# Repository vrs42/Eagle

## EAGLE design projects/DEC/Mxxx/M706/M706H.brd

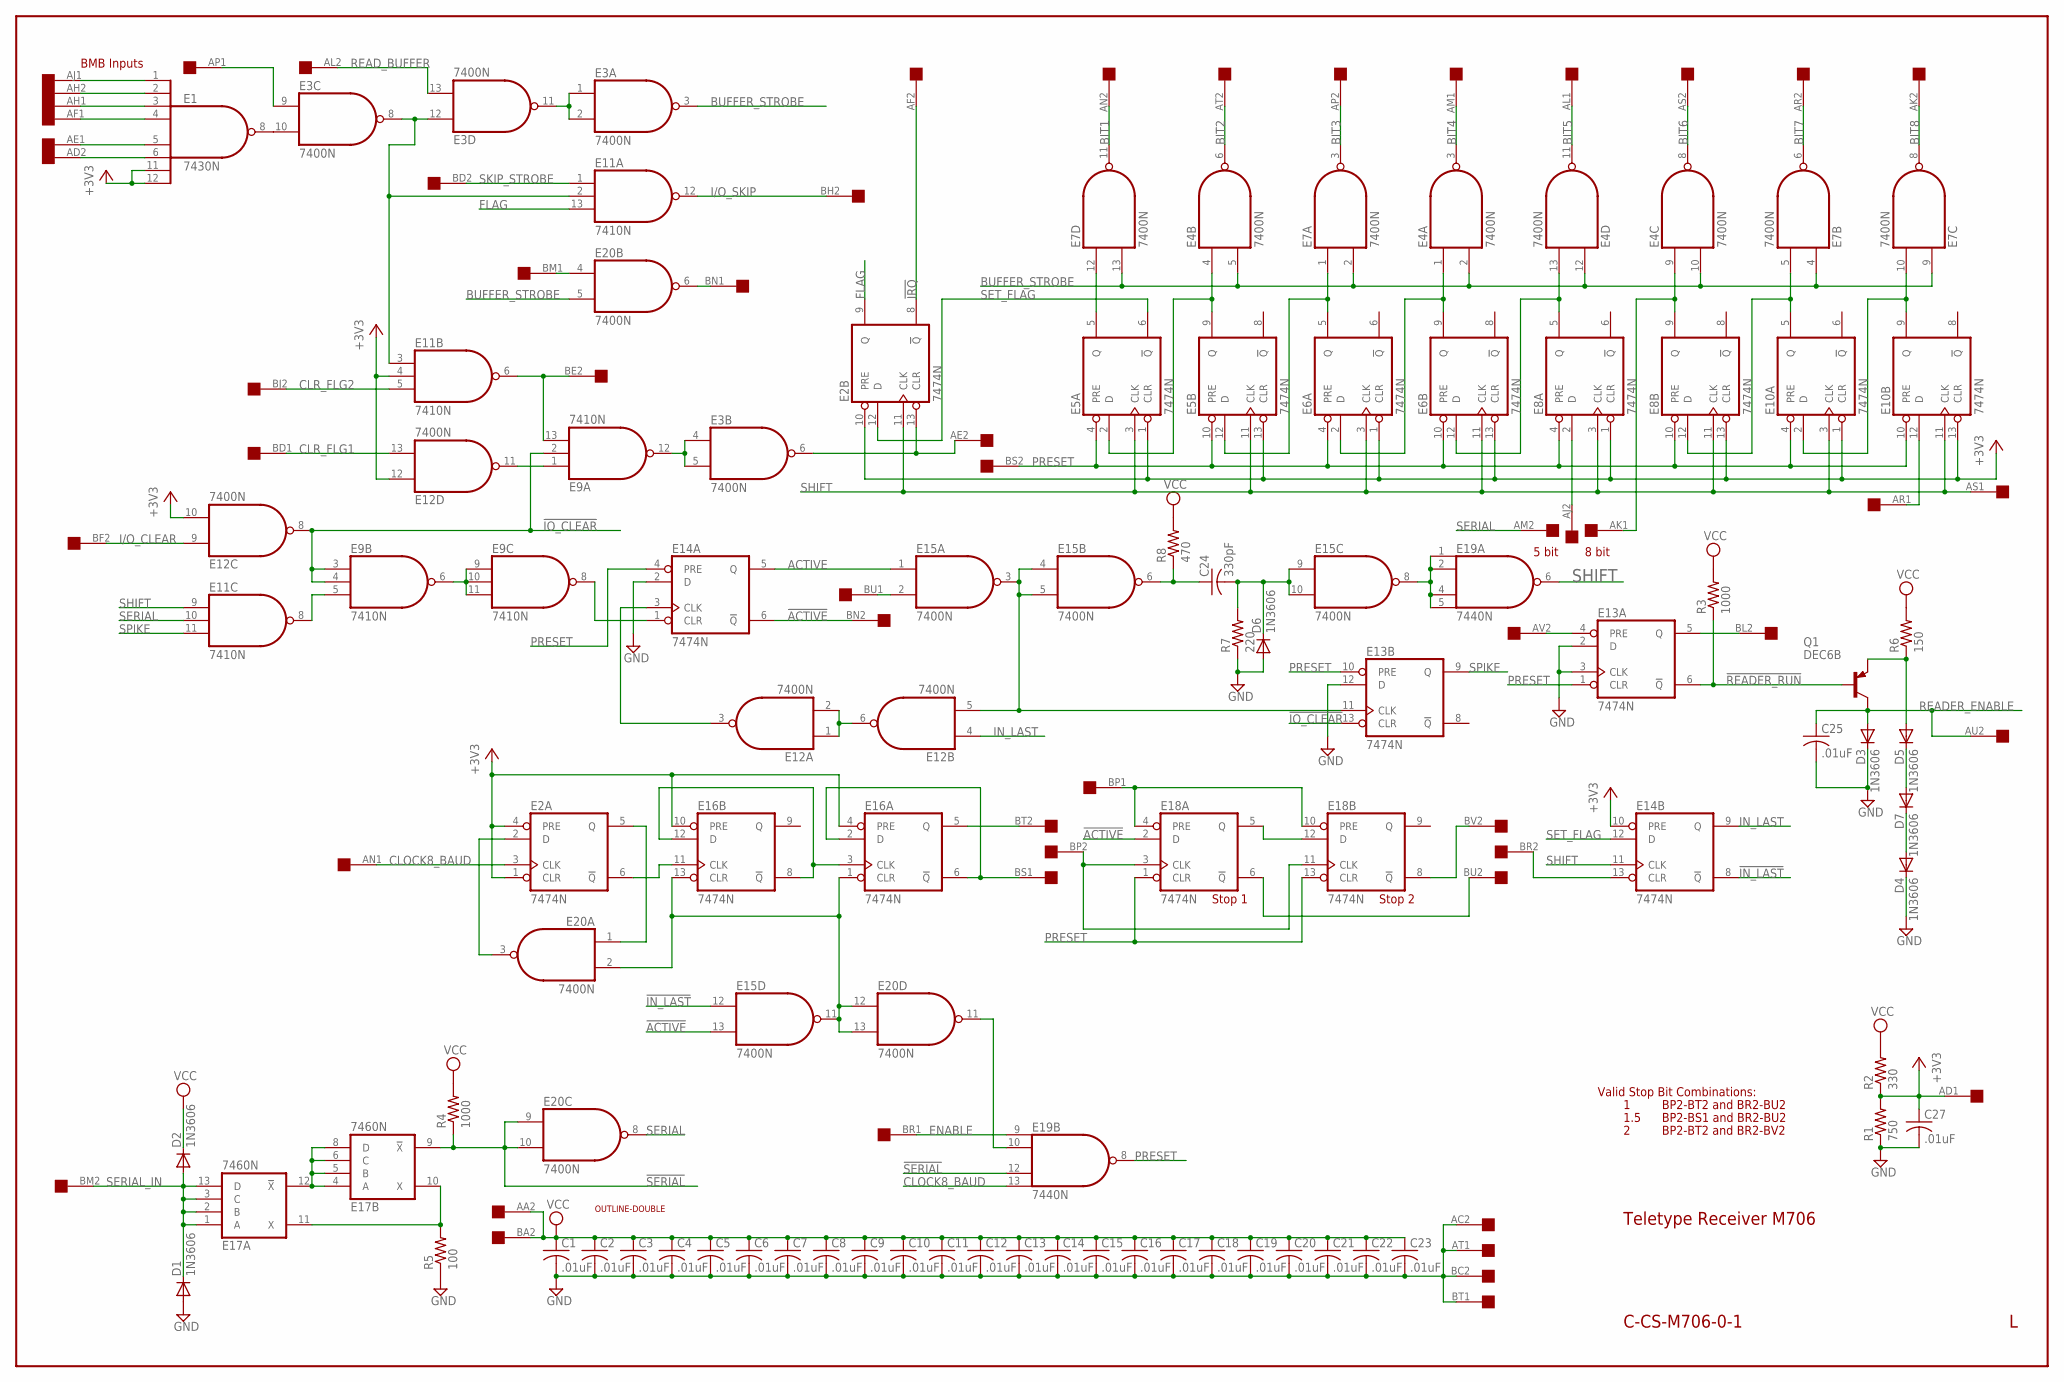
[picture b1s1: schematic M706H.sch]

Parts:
C1, C2, C3, C4, C5, C6, C7, C8, C9, C10, C11, C12, C13, C14, C15, C16, C17, C18, C19, C20, C21, C22, C23, C25, C27: .01uF; C050-025X075
C24: 330pF; C050-025X075
D1, D2, D3, D4, D5, D6, D7: 1N3606; DO35-10
E1: 7430N; DIL14
E2, E5, E6, E8, E10, E13, E14, E16, E18: 7474N; DIL14
E3, E4, E7, E12, E15, E20: 7400N; DIL14
E9, E11: 7410N; DIL14
E17: 7460N; DIL14
E19: 7440N; DIL14
Q1: DEC6B; TO39
R1: 750; 0207/10
R2: 330; 0207/10
R3, R4: 1000; 0207/10
R5: 100; 0207/10
R6: 150; 0207/10
R7: 220; 0207/10
R8: 470; 0207/10
U$1: OUTLINE-DOUBLE; DOUBLE
U$2: DOUBLE; EDGE-CON4

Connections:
2^0: E2.5 (Q), E20.1 (I0)
!ACTIVE: E14.6 (!Q), E15.13 (I1), E18.2 (D), U$2.BN2
!IN_LAST: E14.8 (!Q), E15.12 (I0)
!IO_CLEAR: E9.2 (I1), E9.3 (I0), E9.4 (I1), E12.8 (O), E13.13 (CLR)
!IRQ: E2.8 (!Q), U$2.AF2
!READER_RUN: E13.6 (!Q), Q1.2 (B), R3.1
!SERIAL: E17.9 (!X), E19.12 (I2), E20.9 (I0), E20.10 (I1), R4.1
+3V3: C27.1, E1.11 (I6), E1.12 (I7), E2.1 (CLR), E2.4 (PRE), E2.10 (PRE), E5.1 (CLR), E5.13 (CLR), E6.1 (CLR), E6.13 (CLR), E8.1 (CLR), E8.13 (CLR), E10.1 (CLR), E10.13 (CLR), E11.4 (I1), E12.10 (I1), E12.12 (I0), E14.10 (PRE), E16.4 (PRE), E16.10 (PRE), R1.2, R2.1, U$2.AD1
ACTIVE: E14.5 (Q), E15.1 (I0)
BIT1: E7.11 (O), U$2.AN2
BIT2: E4.6 (O), U$2.AT2
BIT3: E7.3 (O), U$2.AP2
BIT4: E4.3 (O), U$2.AM1
BIT5: E4.11 (O), U$2.AL1
BIT6: E4.8 (O), U$2.AS2
BIT7: E7.6 (O), U$2.AR2
BIT8: E7.8 (O), U$2.AK2
BUFFER_STROBE: E3.3 (O), E4.2 (I1), E4.5 (I1), E4.10 (I1), E4.12 (I0), E7.2 (I1), E7.4 (I0), E7.9 (I0), E7.13 (I1), E20.5 (I1)
CLOCK8_BAUD: E2.3 (CLK), E19.13 (I3), U$2.AN1
CLR_FLG1: E12.13 (I1), U$2.BD1
CLR_FLG2: E11.5 (I2), U$2.BJ2
ENABLE: E19.9 (I0), U$2.BR1
FLAG: E2.9 (Q), E11.13 (I2)
GND: C1.2, C2.2, C3.2, C4.2, C5.2, C6.2, C7.2, C8.2, C9.2, C10.2, C11.2, C12.2, C13.2, C14.2, C15.2, C16.2, C17.2, C18.2, C19.2, C20.2, C21.2, C22.2, C23.2, C25.2, C27.2, D1.A, D3.C, D4.C, D6.A, E1.7 (GND), E2.7 (GND), E3.7 (GND), E4.7 (GND), E5.7 (GND), E6.7 (GND), E7.7 (GND), E8.7 (GND), E9.7 (GND), E10.7 (GND), E11.7 (GND), E12.7 (GND), E13.2 (D), E13.3 (CLK), E13.7 (GND), E13.12 (D), E14.2 (D), E14.7 (GND), E15.7 (GND), E16.7 (GND), E17.7 (GND), E18.7 (GND), E19.7 (GND), E20.7 (GND), R1.1, R5.1, R7.1, U$2.AC2, U$2.AT1, U$2.BC2, U$2.BT1
I/O_CLEAR: E12.9 (I0), U$2.BF2
I/O_SKIP: E11.12 (O), U$2.BH2
IN_LAST: E12.4 (I0), E14.9 (Q)
unnamed: E19.10 (I1), E20.11 (O)
unnamed: E7.5 (I1), E8.12 (D), E10.5 (Q)
unnamed: E7.10 (I1), E10.2 (D), E10.9 (Q)
unnamed: E4.9 (I0), E8.9 (Q), U$2.AK1
unnamed: E5.12 (D), E6.5 (Q), E7.1 (I0)
unnamed: E4.1 (I0), E6.2 (D), E6.9 (Q)
unnamed: E4.13 (I1), E6.12 (D), E8.5 (Q)
unnamed: E5.5 (Q), E7.12 (I0)
unnamed: E4.4 (I0), E5.2 (D), E5.9 (Q)
unnamed: E1.8 (O), E3.10 (I1)
unnamed: E2.13 (CLR), E3.6 (O), U$2.AE2
unnamed: E3.4 (I0), E3.5 (I1), E9.12 (O)
unnamed: E12.3 (O), E14.3 (CLK)
unnamed: E10.12 (D), U$2.AR1
unnamed: E1.1 (I0), U$2.AJ1
unnamed: E3.9 (I0), U$2.AP1
unnamed: E1.6 (I5), U$2.AD2
unnamed: E1.5 (I4), U$2.AE1
unnamed: E1.4 (I3), U$2.AF1
unnamed: E1.3 (I2), U$2.AH1
unnamed: E1.2 (I1), U$2.AH2
unnamed: E3.1 (I0), E3.2 (I1), E3.11 (O)
unnamed: E3.8 (O), E3.12 (I0), E11.2 (I1), E11.3 (I0)
unnamed: E9.1 (I0), E12.11 (O)
unnamed: E9.13 (I2), E11.6 (O), U$2.BE2
unnamed: E15.8 (O), E19.1 (I0), E19.2 (I1), E19.4 (I2), E19.5 (I3)
unnamed: E2.2 (D), E20.3 (O)
unnamed: E9.5 (I2), E11.8 (O)
unnamed: E9.6 (O), E9.9 (I0), E9.10 (I1), E9.11 (I2)
unnamed: E8.2 (D), U$2.AJ2
unnamed: E9.8 (O), E14.1 (CLR)
unnamed: E2.6 (!Q), E16.11 (CLK)
unnamed: E16.3 (CLK), E16.8 (!Q), E16.12 (D)
unnamed: E16.5 (Q), U$2.BT2
unnamed: E16.2 (D), E16.6 (!Q), U$2.BS1
unnamed: E18.3 (CLK), E18.11 (CLK), U$2.BP2
unnamed: E17.4 (A), E17.5 (B), E17.6 (C), E17.8 (D), E17.12 (!X)
unnamed: E17.10 (X), E17.11 (X), R5.2
unnamed: E12.1 (I0), E12.2 (I1), E12.6 (O)
unnamed: E12.5 (I1), E13.11 (CLK), E15.3 (O), E15.4 (I0), E15.5 (I1)
unnamed: E15.11 (O), E16.1 (CLR), E16.13 (CLR), E20.2 (I1), E20.12 (I0), E20.13 (I1)
unnamed: E20.6 (O), U$2.BN1
unnamed: E20.4 (I0), U$2.BM1
unnamed: C24.1, E15.6 (O), R8.1
unnamed: E13.4 (PRE), U$2.AV2
unnamed: E13.5 (Q), U$2.BL2
unnamed: C24.2, D6.C, E15.9 (I0), E15.10 (I1), R7.2
unnamed: D5.A, Q1.1 (E), R6.1
unnamed: D5.C, D7.A
unnamed: D4.A, D7.C
unnamed: E14.13 (CLR), U$2.BR2
unnamed: E18.6 (!Q), U$2.BU2
unnamed: E18.8 (!Q), U$2.BV2
unnamed: E18.5 (Q), E18.12 (D)
unnamed: E18.4 (PRE), E18.10 (PRE), U$2.BP1
unnamed: E15.2 (I1), U$2.BU1
PRESET: E5.4 (PRE), E5.10 (PRE), E6.4 (PRE), E6.10 (PRE), E8.4 (PRE), E8.10 (PRE), E10.4 (PRE), E10.10 (PRE), E13.1 (CLR), E13.10 (PRE), E14.4 (PRE), E18.1 (CLR), E18.13 (CLR), E19.8 (O), U$2.BS2
READER_ENABLE: C25.1, D3.A, Q1.3 (C), U$2.AU2
READ_BUFFER: E3.13 (I1), U$2.AL2
SERIAL: E11.10 (I1), E20.8 (O), U$2.AM2
SERIAL_IN: D1.C, D2.A, E17.1 (A), E17.2 (B), E17.3 (C), E17.13 (D), U$2.BM2
SET_FLAG: E2.12 (D), E5.6 (!Q), E14.12 (D)
SHIFT: E2.11 (CLK), E5.3 (CLK), E5.11 (CLK), E6.3 (CLK), E6.11 (CLK), E8.3 (CLK), E8.11 (CLK), E10.3 (CLK), E10.11 (CLK), E11.9 (I0), E14.11 (CLK), E19.6 (O), U$2.AS1
SKIP_STROBE: E11.1 (I0), U$2.BD2
SPIKE: E11.11 (I2), E13.9 (Q)
VCC: C1.1, C2.1, C3.1, C4.1, C5.1, C6.1, C7.1, C8.1, C9.1, C10.1, C11.1, C12.1, C13.1, C14.1, C15.1, C16.1, C17.1, C18.1, C19.1, C20.1, C21.1, C22.1, C23.1, D2.C, E1.14 (VCC), E2.14 (VCC), E3.14 (VCC), E4.14 (VCC), E5.14 (VCC), E6.14 (VCC), E7.14 (VCC), E8.14 (VCC), E9.14 (VCC), E10.14 (VCC), E11.14 (VCC), E12.14 (VCC), E13.14 (VCC), E14.14 (VCC), E15.14 (VCC), E16.14 (VCC), E17.14 (VCC), E18.14 (VCC), E19.14 (VCC), E20.14 (VCC), R2.2, R3.2, R4.2, R6.2, R8.2, U$2.AA2, U$2.BA2

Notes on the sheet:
BMB Inputs
8 bit
5 bit
Stop 1
Stop 2
Valid Stop Bit Combinations:
1.5
BP2-BT2 and BR2-BU2
BP2-BS1 and BR2-BU2
BP2-BT2 and BR2-BV2
Teletype Receiver M706
C-CS-M706-0-1

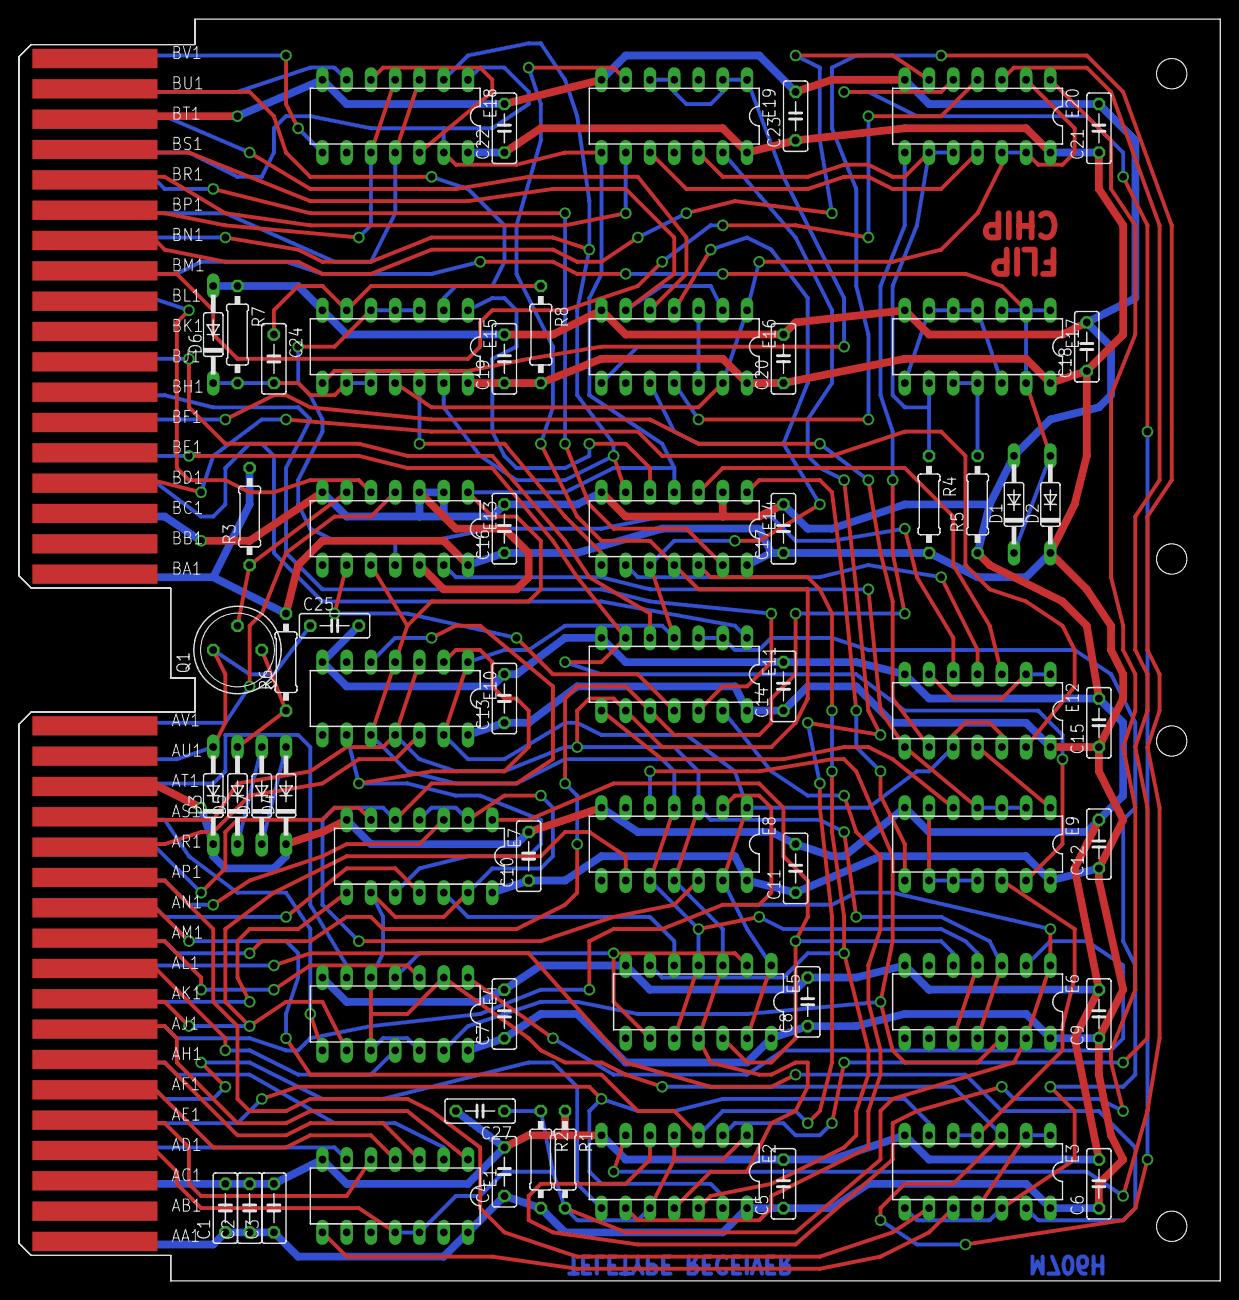
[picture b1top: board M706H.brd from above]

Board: 2 copper layers, 125.7 x 132.1 mm, 64 parts (0 on the bottom side), 93 nets.

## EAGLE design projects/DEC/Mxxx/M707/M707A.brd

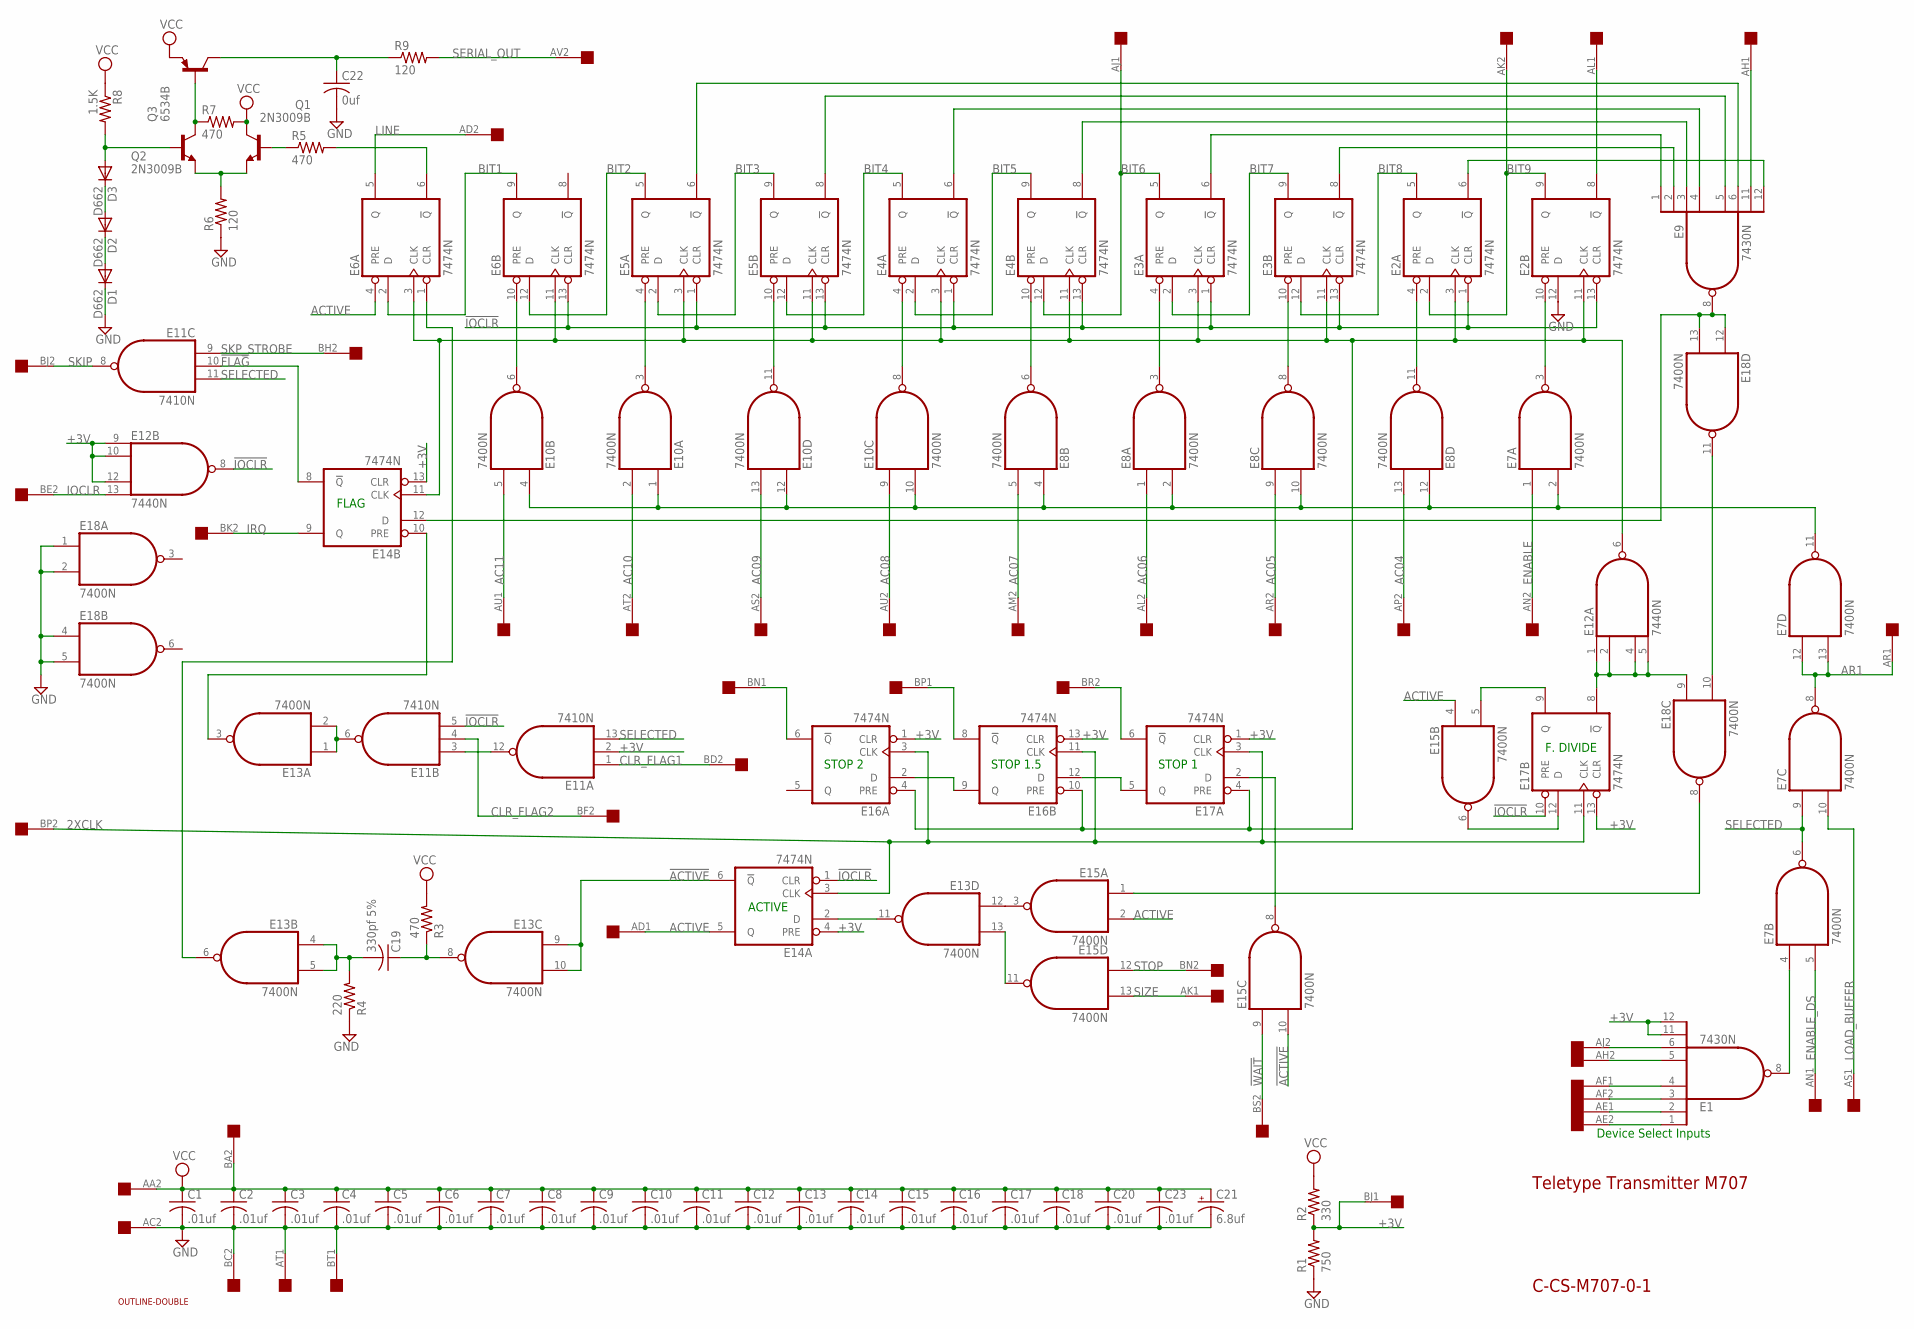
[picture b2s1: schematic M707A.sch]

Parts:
C1, C2, C3, C4, C5, C6, C7, C8, C9, C10, C11, C12, C13, C14, C15, C16, C17, C18, C20, C23: .01uf; C075-032X103
C19: 330pf 5%; C150-054X183
C21: 6.8uf; E15-5
C22: 0uf; C075-032X103
D1, D2, D3: D662; SOD61B
E1, E9: 7430N; DIL14
E2, E3, E4, E5, E6, E14, E16, E17: 7474N; DIL14
E7, E8, E10, E13, E15, E18: 7400N; DIL14
E11: 7410N; DIL14
E12: 7440N; DIL14
Q1, Q2: 2N3009B; TO92-CBE
Q3: 6534B; TO92-CBE
R1: 750; 0207/15
R2: 330; 0207/15
R3, R5, R7: 470; 0207/10
R4: 220; 0207/10
R6: 120; 0207/15
R8: 1.5K; 0207/15
R9: 120; 0207/10
U$1: OUTLINE-DOUBLE; DOUBLE
U$2: DOUBLE; EDGE-CON4

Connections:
2XCLK: E14.3 (CLK), E16.3 (CLK), E16.11 (CLK), E17.3 (CLK), E17.11 (CLK), U$2.BP2
!ACTIVE: E13.9 (I0), E13.10 (I1), E14.6 (!Q), E15.10 (I1)
!FLAG: E11.10 (I1), E14.8 (!Q)
!IOCLR: E2.1 (CLR), E2.13 (CLR), E3.1 (CLR), E3.13 (CLR), E4.1 (CLR), E4.13 (CLR), E5.1 (CLR), E5.13 (CLR), E6.13 (CLR), E11.5 (I2), E12.8 (O), E14.1 (CLR), E17.10 (PRE)
!WAIT: E15.9 (I0), U$2.BS2
+3V: E1.11 (I6), E1.12 (I7), E11.2 (I1), E12.9 (I0), E12.10 (I1), E12.12 (I2), E14.4 (PRE), E14.13 (CLR), E16.1 (CLR), E16.13 (CLR), E17.1 (CLR), E17.13 (CLR), R1.2, R2.1, U$2.BJ1
AC04: E8.13 (I1), U$2.AP2
AC05: E8.9 (I0), U$2.AR2
AC06: E8.1 (I0), U$2.AL2
AC07: E8.5 (I1), U$2.AM2
AC08: E10.9 (I0), U$2.AU2
AC09: E10.13 (I1), U$2.AS2
AC10: E10.2 (I1), U$2.AT2
AC11: E10.5 (I1), U$2.AU1
ACTIVE: E6.4 (PRE), E14.5 (Q), E15.2 (I1), E15.4 (I0), U$2.AD1
AE1: E1.2 (I1), U$2.AE1
AF1: E1.4 (I3), U$2.AF1
AH1: E9.11 (I6), U$2.AH1
AL1: E2.8 (!Q), U$2.AL1
AR1: E7.8 (O), E7.12 (I0), E7.13 (I1), U$2.AR1
BIT1: E6.2 (D), E6.9 (Q)
BIT2: E5.5 (Q), E6.12 (D)
BIT3: E5.2 (D), E5.9 (Q)
BIT4: E4.5 (Q), E5.12 (D)
BIT5: E4.2 (D), E4.9 (Q)
BIT6: E3.5 (Q), E4.12 (D), U$2.AJ1
BIT7: E3.2 (D), E3.9 (Q)
BIT8: E2.5 (Q), E3.12 (D)
BIT9: E2.2 (D), E2.9 (Q), U$2.AK2
BN1: E16.6 (!Q), U$2.BN1
BP1: E16.8 (!Q), U$2.BP1
CLR_FLAG1: E11.1 (I0), U$2.BD2
CLR_FLAG2: E11.4 (I1), U$2.BF2
ENABLE: E7.1 (I0), U$2.AN2
ENABLE_DS: E7.5 (I1), U$2.AN1
GND: C1.2, C2.2, C3.2, C4.2, C5.2, C6.2, C7.2, C8.2, C9.2, C10.2, C11.2, C12.2, C13.2, C14.2, C15.2, C16.2, C17.2, C18.2, C20.2, C21.-, C22.2, C23.2, D1.C, E1.7 (GND), E2.7 (GND), E2.12 (D), E3.7 (GND), E4.7 (GND), E5.7 (GND), E6.7 (GND), E7.7 (GND), E8.7 (GND), E9.7 (GND), E10.7 (GND), E11.7 (GND), E12.7 (GND), E13.7 (GND), E14.7 (GND), E15.7 (GND), E16.7 (GND), E17.7 (GND), E18.1 (I0), E18.2 (I1), E18.4 (I0), E18.5 (I1), E18.7 (GND), R1.1, R4.1, R6.1, U$2.AC2, U$2.AT1, U$2.BC2, U$2.BT1
IOCLR: E12.13 (I3), U$2.BE2
IRQ: E14.9 (Q), U$2.BK2
LINE: E6.5 (Q), U$2.AD2
LOAD_BUFFER: E7.10 (I1), U$2.AS1
unnamed: C19.1, E13.8 (O), R3.1
unnamed: C19.2, E13.4 (I0), E13.5 (I1), R4.2
unnamed: E2.4 (PRE), E8.11 (O)
unnamed: E6.1 (CLR), E13.6 (O)
unnamed: E2.3 (CLK), E2.11 (CLK), E3.3 (CLK), E3.11 (CLK), E4.3 (CLK), E4.11 (CLK), E5.3 (CLK), E5.11 (CLK), E6.3 (CLK), E6.11 (CLK), E12.6 (O), E14.11 (CLK), E16.4 (PRE), E16.10 (PRE), E17.4 (PRE)
unnamed: E9.8 (O), E14.12 (D), E18.12 (I0), E18.13 (I1)
unnamed: E2.6 (!Q), E9.12 (I7)
unnamed: C22.1, Q3.C, R9.1
unnamed: E1.8 (O), E7.4 (I0)
unnamed: E1.6 (I5), U$2.AJ2
unnamed: E1.5 (I4), U$2.AH2
unnamed: E1.3 (I2), U$2.AF2
unnamed: E1.1 (I0), U$2.AE2
unnamed: E7.2 (I1), E7.11 (O), E8.2 (I1), E8.4 (I0), E8.10 (I1), E8.12 (I0), E10.1 (I0), E10.4 (I0), E10.10 (I1), E10.12 (I0)
unnamed: E2.10 (PRE), E7.3 (O)
unnamed: D1.A, D2.C
unnamed: D2.A, D3.C
unnamed: Q1.B, R5.1
unnamed: Q2.C, Q3.B, R7.1
unnamed: Q1.E, Q2.E, R6.2
unnamed: D3.A, Q2.B, R8.2
unnamed: E6.6 (!Q), R5.2
unnamed: E13.13 (I1), E15.11 (O)
unnamed: E17.6 (!Q), U$2.BR2
unnamed: E3.4 (PRE), E8.3 (O)
unnamed: E15.1 (I0), E18.8 (O)
unnamed: E13.12 (I0), E15.3 (O)
unnamed: E11.3 (I0), E11.12 (O)
unnamed: E12.1 (I0), E12.2 (I1), E12.4 (I2), E12.5 (I3), E17.8 (!Q), E18.9 (I0)
unnamed: E16.2 (D), E16.9 (Q)
unnamed: E3.6 (!Q), E9.1 (I0)
unnamed: E4.4 (PRE), E10.8 (O)
unnamed: E3.8 (!Q), E9.2 (I1)
unnamed: E4.8 (!Q), E9.3 (I2)
unnamed: E4.6 (!Q), E9.4 (I3)
unnamed: E5.8 (!Q), E9.5 (I4)
unnamed: E5.6 (!Q), E9.6 (I5)
unnamed: E15.8 (O), E17.2 (D)
unnamed: E11.6 (O), E13.1 (I0), E13.2 (I1)
unnamed: E16.12 (D), E17.5 (Q)
unnamed: E13.3 (O), E14.10 (PRE)
unnamed: E5.4 (PRE), E10.3 (O)
unnamed: E13.11 (O), E14.2 (D)
unnamed: E15.6 (O), E17.12 (D)
unnamed: E15.5 (I1), E17.9 (Q)
unnamed: E3.10 (PRE), E8.8 (O)
unnamed: E4.10 (PRE), E8.6 (O)
unnamed: E5.10 (PRE), E10.11 (O)
unnamed: E6.10 (PRE), E10.6 (O)
unnamed: E18.10 (I1), E18.11 (O)
SELECTED: E7.6 (O), E7.9 (I0), E11.11 (I2), E11.13 (I2)
SERIAL_OUT: R9.2, U$2.AV2
SIZE: E15.13 (I1), U$2.AK1
SKIP: E11.8 (O), U$2.BJ2
SKP_STROBE: E11.9 (I0), U$2.BH2
STOP: E15.12 (I0), U$2.BN2
VCC: C1.1, C2.1, C3.1, C4.1, C5.1, C6.1, C7.1, C8.1, C9.1, C10.1, C11.1, C12.1, C13.1, C14.1, C15.1, C16.1, C17.1, C18.1, C20.1, C21.+, C23.1, E1.14 (VCC), E2.14 (VCC), E3.14 (VCC), E4.14 (VCC), E5.14 (VCC), E6.14 (VCC), E7.14 (VCC), E8.14 (VCC), E9.14 (VCC), E10.14 (VCC), E11.14 (VCC), E12.14 (VCC), E13.14 (VCC), E14.14 (VCC), E15.14 (VCC), E16.14 (VCC), E17.14 (VCC), E18.14 (VCC), Q1.C, Q3.E, R2.2, R3.2, R7.2, R8.1, U$2.AA2, U$2.BA2

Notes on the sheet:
C-CS-M707-0-1
Teletype Transmitter M707
Device Select Inputs
F. DIVIDE
FLAG
ACTIVE
STOP 2
STOP 1.5
STOP 1

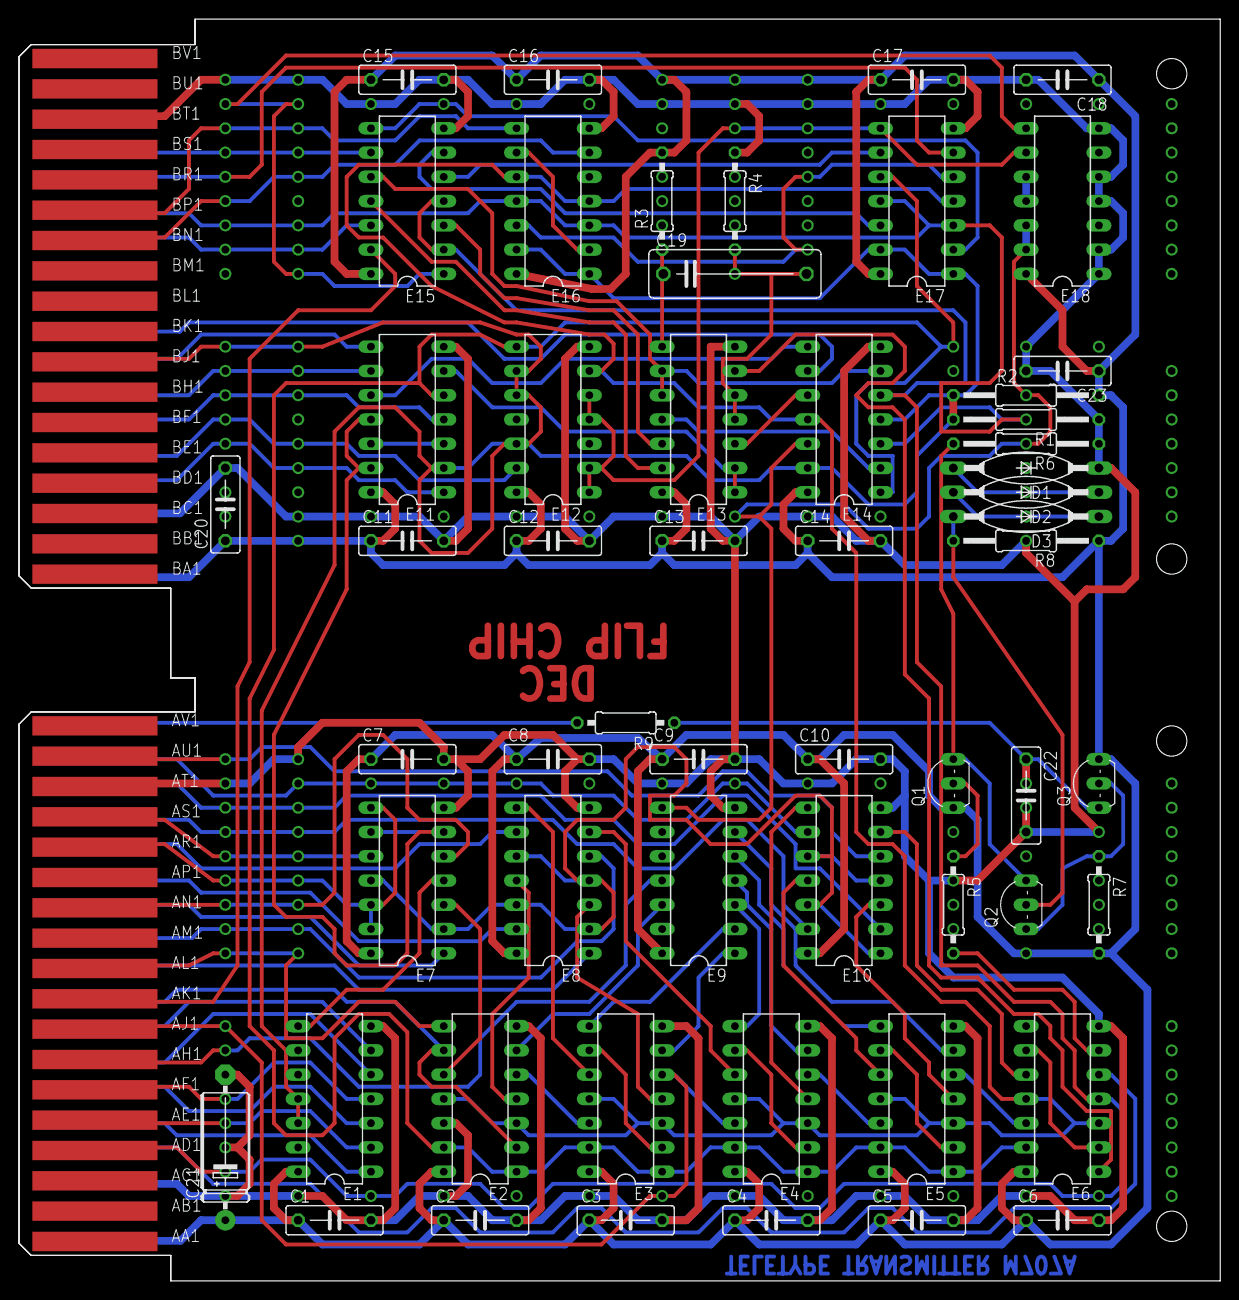
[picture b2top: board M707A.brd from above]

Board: 2 copper layers, 125.7 x 132.1 mm, 58 parts (0 on the bottom side), 97 nets.
